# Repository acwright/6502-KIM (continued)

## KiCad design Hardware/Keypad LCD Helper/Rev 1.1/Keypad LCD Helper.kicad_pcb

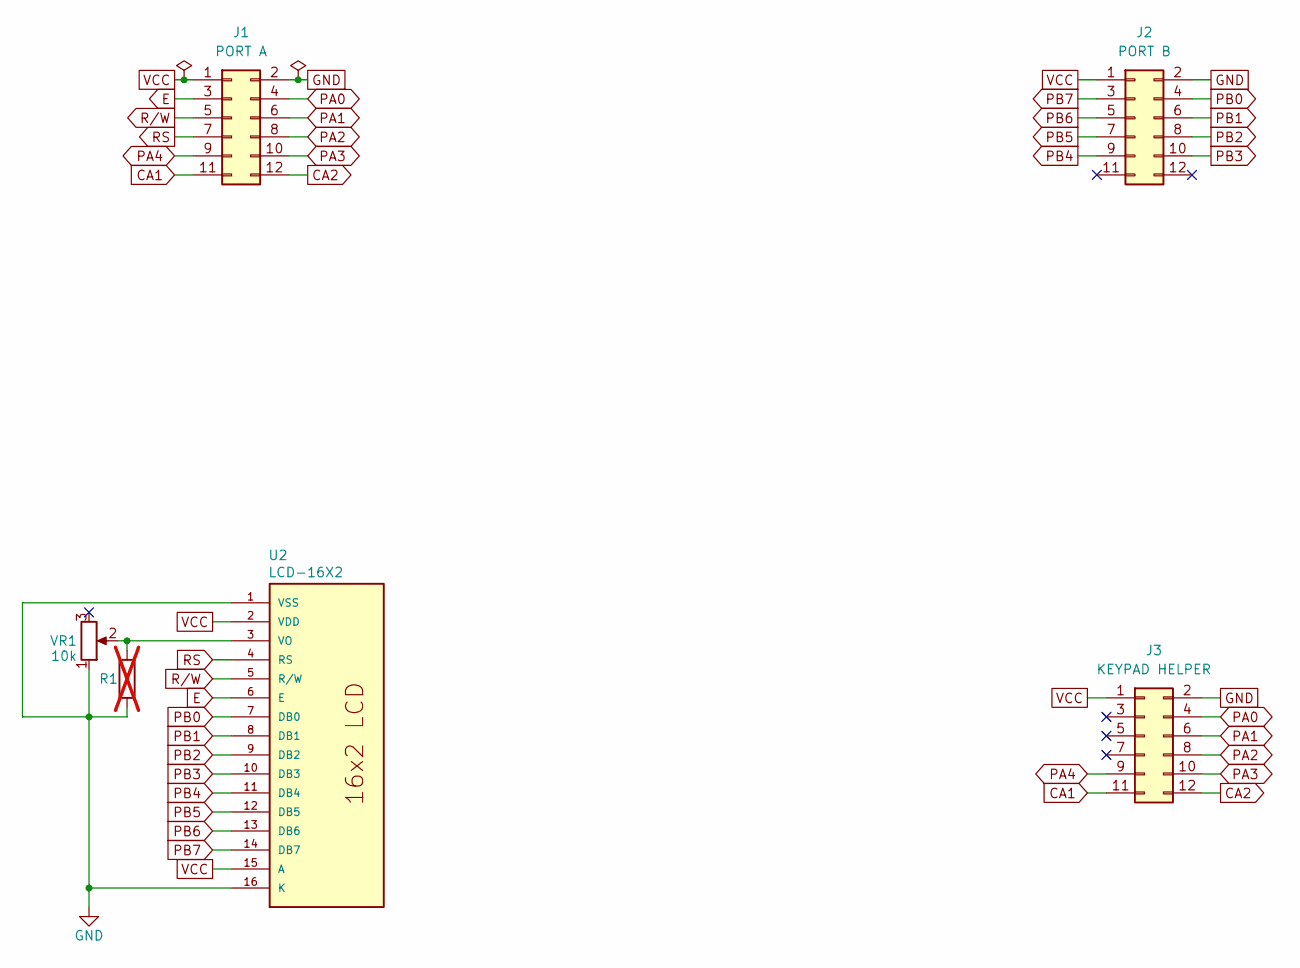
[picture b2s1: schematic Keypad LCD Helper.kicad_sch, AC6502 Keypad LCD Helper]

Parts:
J1: PORT A; 6502 GPIO Connector; Digikey 2057-BHR-12-VUA-ND
J2: PORT B; 6502 GPIO Connector; Digikey 2057-BHR-12-VUA-ND
J3: KEYPAD HELPER; 6502 GPIO Connector; Digikey 2057-BHR-12-VUA-ND
R1: DNP: parallel with VR1 to make ~10 k; R_Axial_DIN0204_L3.6mm_D1.6mm_P5.08mm_Horizontal; not fitted
U2: LCD-16X2
VR1: 10k; Trimmer 3386F; Digikey 3386F-103LF-ND

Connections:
CA1: J1.11, J3.11
CA2: J1.12, J3.12
E: J1.3, U2.6 (E)
GND: J1.2, J2.2, J3.2, R1.2, U2.1 (VSS), U2.16 (K), VR1.1
unnamed: R1.1, U2.3 (VO), VR1.2
PA0: J1.4, J3.4
PA1: J1.6, J3.6
PA2: J1.8, J3.8
PA3: J1.10, J3.10
PA4: J1.9, J3.9
PB0: J2.4, U2.7 (DB0)
PB1: J2.6, U2.8 (DB1)
PB2: J2.8, U2.9 (DB2)
PB3: J2.10, U2.10 (DB3)
PB4: J2.9, U2.11 (DB4)
PB5: J2.7, U2.12 (DB5)
PB6: J2.5, U2.13 (DB6)
PB7: J2.3, U2.14 (DB7)
RS: J1.7, U2.4 (RS)
R/W: J1.5, U2.5 (R/W)
VCC: J1.1, J2.1, J3.1, U2.2 (VDD), U2.15 (A)

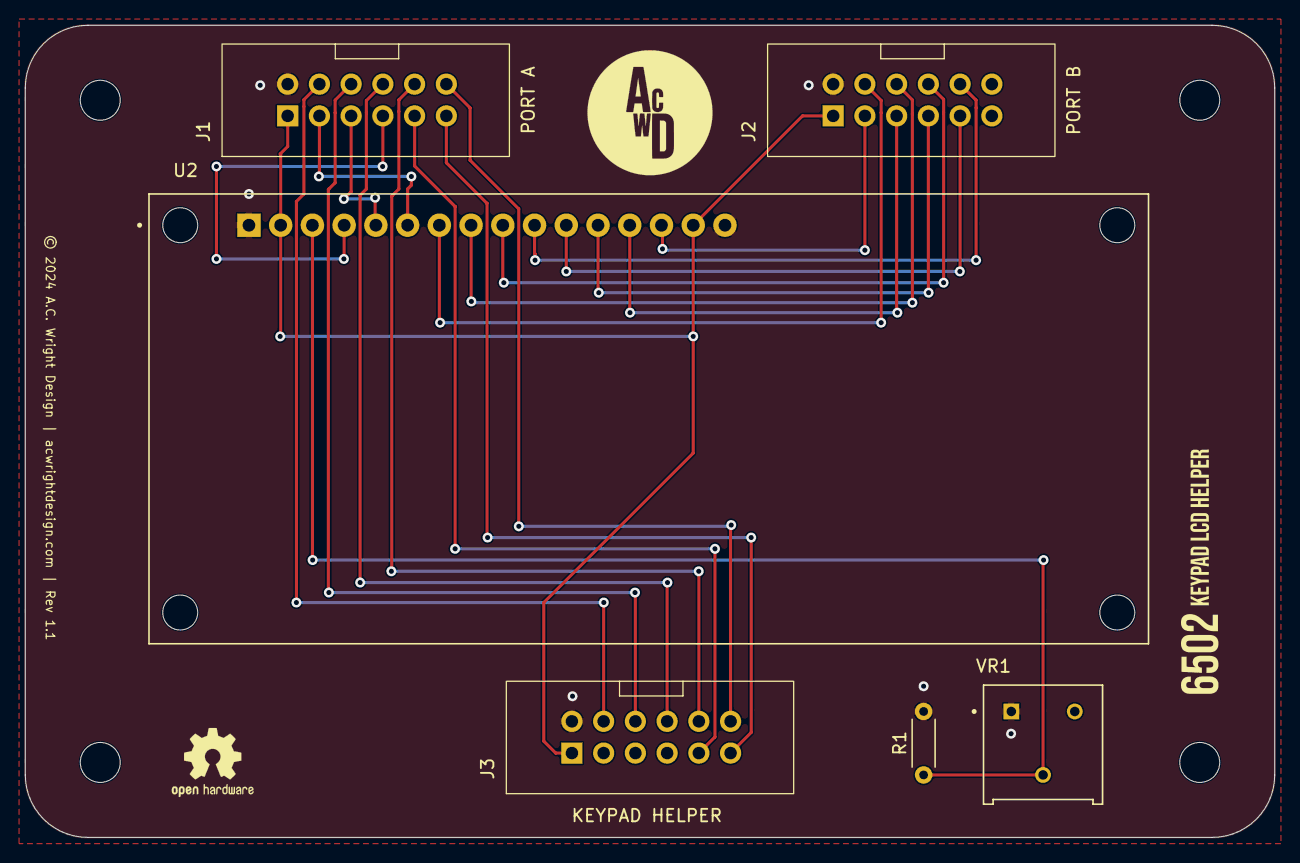
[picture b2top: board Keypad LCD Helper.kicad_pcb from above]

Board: 2 copper layers, 100.0 x 65.0 mm, 10 parts (0 on the bottom side), 21 nets.

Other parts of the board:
H1, H2, H3, H4: MountingHole; MountingHole_3.2mm_M3

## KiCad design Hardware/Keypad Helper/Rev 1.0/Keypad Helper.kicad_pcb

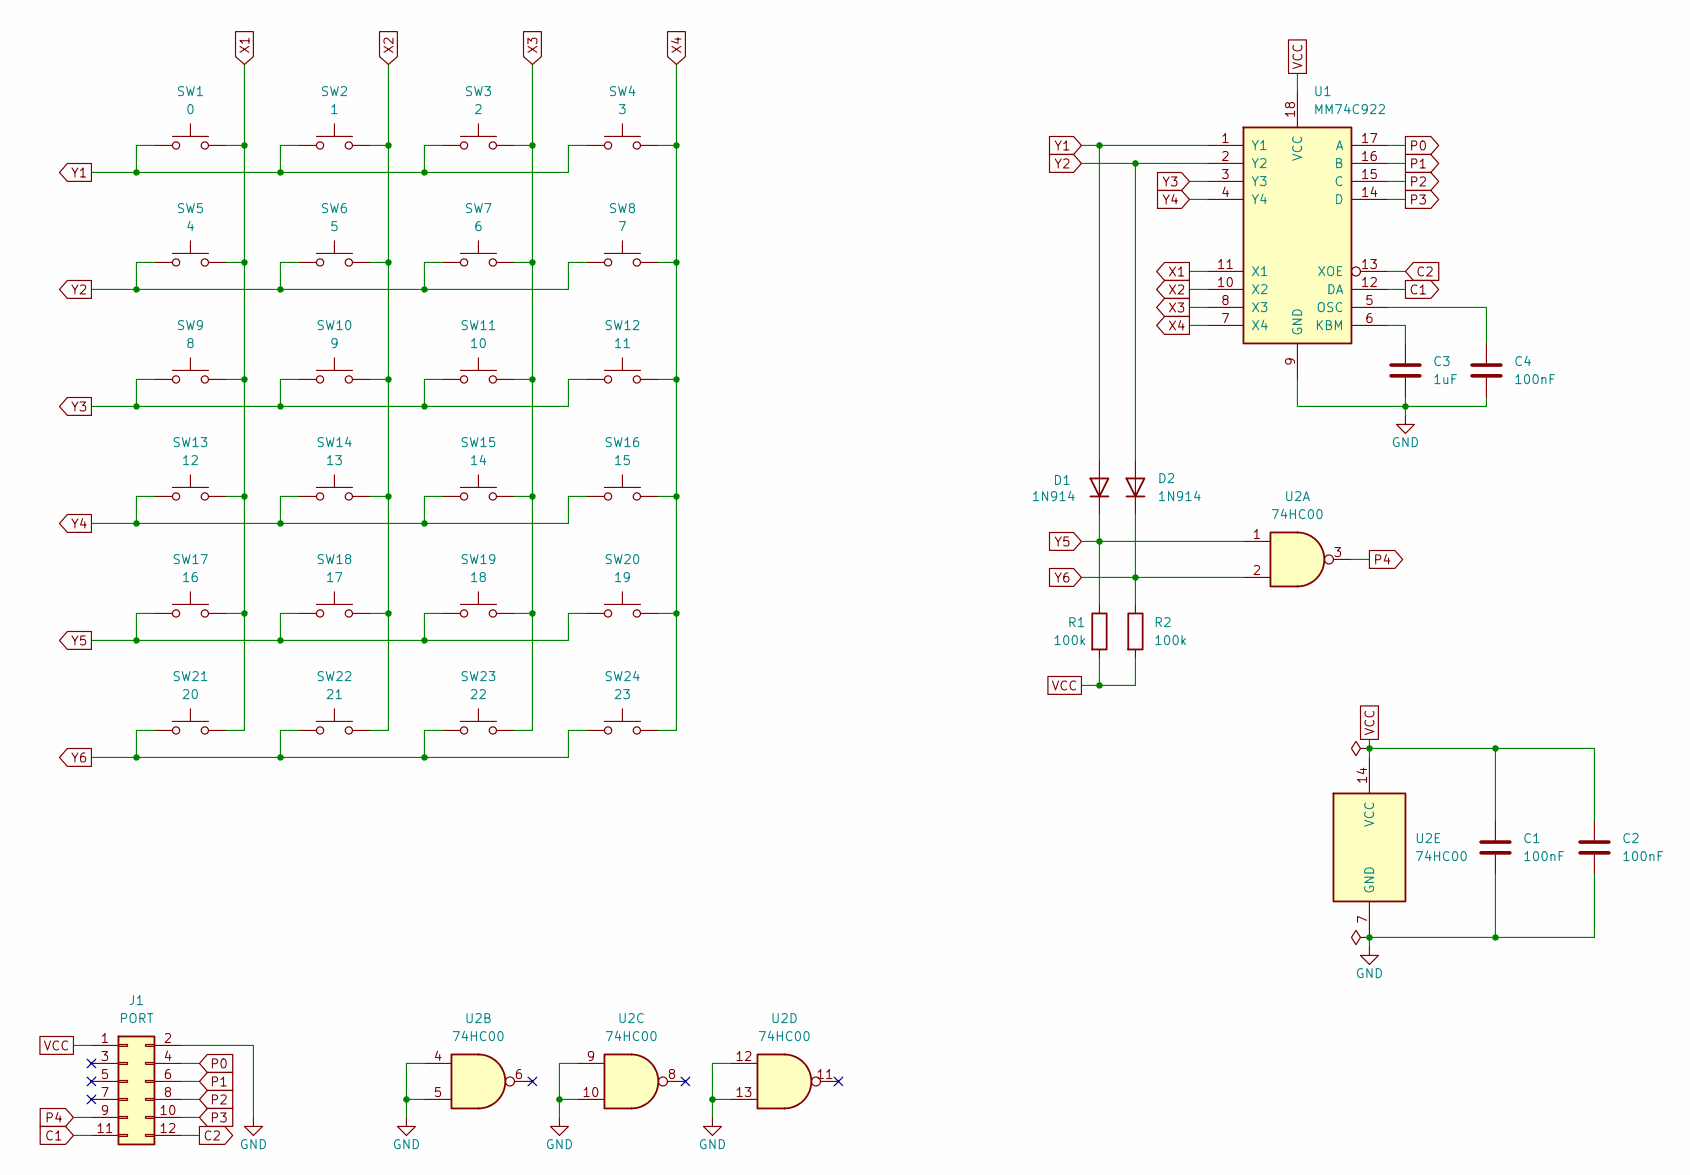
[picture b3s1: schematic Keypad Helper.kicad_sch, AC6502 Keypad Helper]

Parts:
C1, C2, C4: 100nF; C_Disc_D5.0mm_W2.5mm_P5.00mm; Digikey 478-3188-ND
C3: 1uF; C_Disc_D5.0mm_W2.5mm_P5.00mm; Digikey 478-SR215C105KAR-ND
D1, D2: 1N914; D_DO-35_SOD27_P7.62mm_Horizontal; Digikey 1N914FS-ND
J1: PORT; 6502 GPIO Connector; Digikey 2057-BHR-12-VUA-ND
R1, R2: 100k; R_Axial_DIN0204_L3.6mm_D1.6mm_P5.08mm_Horizontal; Digikey 13-MFR-12FTF52-100KCT-ND
SW1: 0; SW_Cherry_MX_1.00u_PCB; Digikey 1644-MX2A-E1NA-ND
SW2: 1; SW_Cherry_MX_1.00u_PCB; Digikey 1644-MX2A-E1NA-ND
SW3: 2; SW_Cherry_MX_1.00u_PCB; Digikey 1644-MX2A-E1NA-ND
SW4: 3; SW_Cherry_MX_1.00u_PCB; Digikey 1644-MX2A-E1NA-ND
SW5: 4; SW_Cherry_MX_1.00u_PCB; Digikey 1644-MX2A-E1NA-ND
SW6: 5; SW_Cherry_MX_1.00u_PCB; Digikey 1644-MX2A-E1NA-ND
SW7: 6; SW_Cherry_MX_1.00u_PCB; Digikey 1644-MX2A-E1NA-ND
SW8: 7; SW_Cherry_MX_1.00u_PCB; Digikey 1644-MX2A-E1NA-ND
SW9: 8; SW_Cherry_MX_1.00u_PCB; Digikey 1644-MX2A-E1NA-ND
SW10: 9; SW_Cherry_MX_1.00u_PCB; Digikey 1644-MX2A-E1NA-ND
SW11: 10; SW_Cherry_MX_1.00u_PCB; Digikey 1644-MX2A-E1NA-ND
SW12: 11; SW_Cherry_MX_1.00u_PCB; Digikey 1644-MX2A-E1NA-ND
SW13: 12; SW_Cherry_MX_1.00u_PCB; Digikey 1644-MX2A-E1NA-ND
SW14: 13; SW_Cherry_MX_1.00u_PCB; Digikey 1644-MX2A-E1NA-ND
SW15: 14; SW_Cherry_MX_1.00u_PCB; Digikey 1644-MX2A-E1NA-ND
SW16: 15; SW_Cherry_MX_1.00u_PCB; Digikey 1644-MX2A-E1NA-ND
SW17: 16; SW_Cherry_MX_1.00u_PCB; Digikey 1644-MX2A-E1NA-ND
SW18: 17; SW_Cherry_MX_1.00u_PCB; Digikey 1644-MX2A-E1NA-ND
SW19: 18; SW_Cherry_MX_1.00u_PCB; Digikey 1644-MX2A-E1NA-ND
SW20: 19; SW_Cherry_MX_1.00u_PCB; Digikey 1644-MX2A-E1NA-ND
SW21: 20; SW_Cherry_MX_1.00u_PCB; Digikey 1644-MX2A-E1NA-ND
SW22: 21; SW_Cherry_MX_1.00u_PCB; Digikey 1644-MX2A-E1NA-ND
SW23: 22; SW_Cherry_MX_1.00u_PCB; Digikey 1644-MX2A-E1NA-ND
SW24: 23; SW_Cherry_MX_1.00u_PCB; Digikey 1644-MX2A-E1NA-ND
U1: MM74C922; DIP-18_W7.62mm_LongPads
U2: 74HC00; DIP-14_W7.62mm_LongPads; Digikey 296-1563-5-ND

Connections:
C1: J1.11, U1.12 (DA)
C2: J1.12, U1.13 (XOE)
GND: C1.2, C2.2, C3.2, C4.2, J1.2, U1.9 (GND), U2.4, U2.5, U2.7 (GND), U2.9, U2.10, U2.12, U2.13
unnamed: C3.1, U1.6 (KBM)
unnamed: C4.1, U1.5 (OSC)
P0: J1.4, U1.17 (A)
P1: J1.6, U1.16 (B)
P2: J1.8, U1.15 (C)
P3: J1.10, U1.14 (D)
P4: J1.9, U2.3
VCC: C1.1, C2.1, J1.1, R1.2, R2.2, U1.18 (VCC), U2.14 (VCC)
X1: SW1.2, SW5.2, SW9.2, SW13.2, SW17.2, SW21.2, U1.11 (X1)
X2: SW2.2, SW6.2, SW10.2, SW14.2, SW18.2, SW22.2, U1.10 (X2)
X3: SW3.2, SW7.2, SW11.2, SW15.2, SW19.2, SW23.2, U1.8 (X3)
X4: SW4.2, SW8.2, SW12.2, SW16.2, SW20.2, SW24.2, U1.7 (X4)
Y1: D1.2 (A), SW1.1, SW2.1, SW3.1, SW4.1, U1.1 (Y1)
Y2: D2.2 (A), SW5.1, SW6.1, SW7.1, SW8.1, U1.2 (Y2)
Y3: SW9.1, SW10.1, SW11.1, SW12.1, U1.3 (Y3)
Y4: SW13.1, SW14.1, SW15.1, SW16.1, U1.4 (Y4)
Y5: D1.1 (K), R1.1, SW17.1, SW18.1, SW19.1, SW20.1, U2.1
Y6: D2.1 (K), R2.1, SW21.1, SW22.1, SW23.1, SW24.1, U2.2

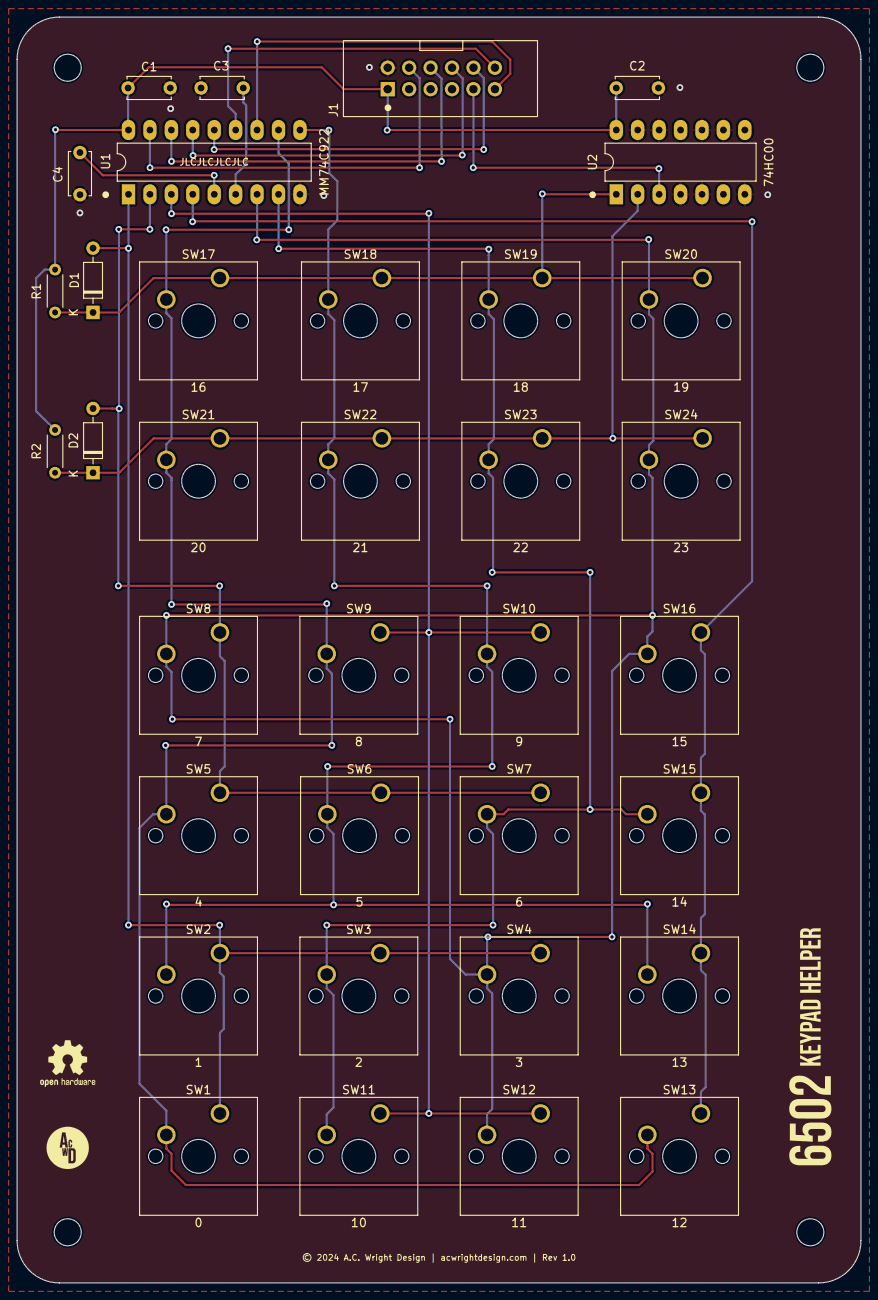
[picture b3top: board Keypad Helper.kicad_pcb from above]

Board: 2 copper layers, 100.0 x 150.0 mm, 39 parts (0 on the bottom side), 21 nets.

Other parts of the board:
H1, H2, H3, H4: MountingHole; MountingHole_3.2mm_M3

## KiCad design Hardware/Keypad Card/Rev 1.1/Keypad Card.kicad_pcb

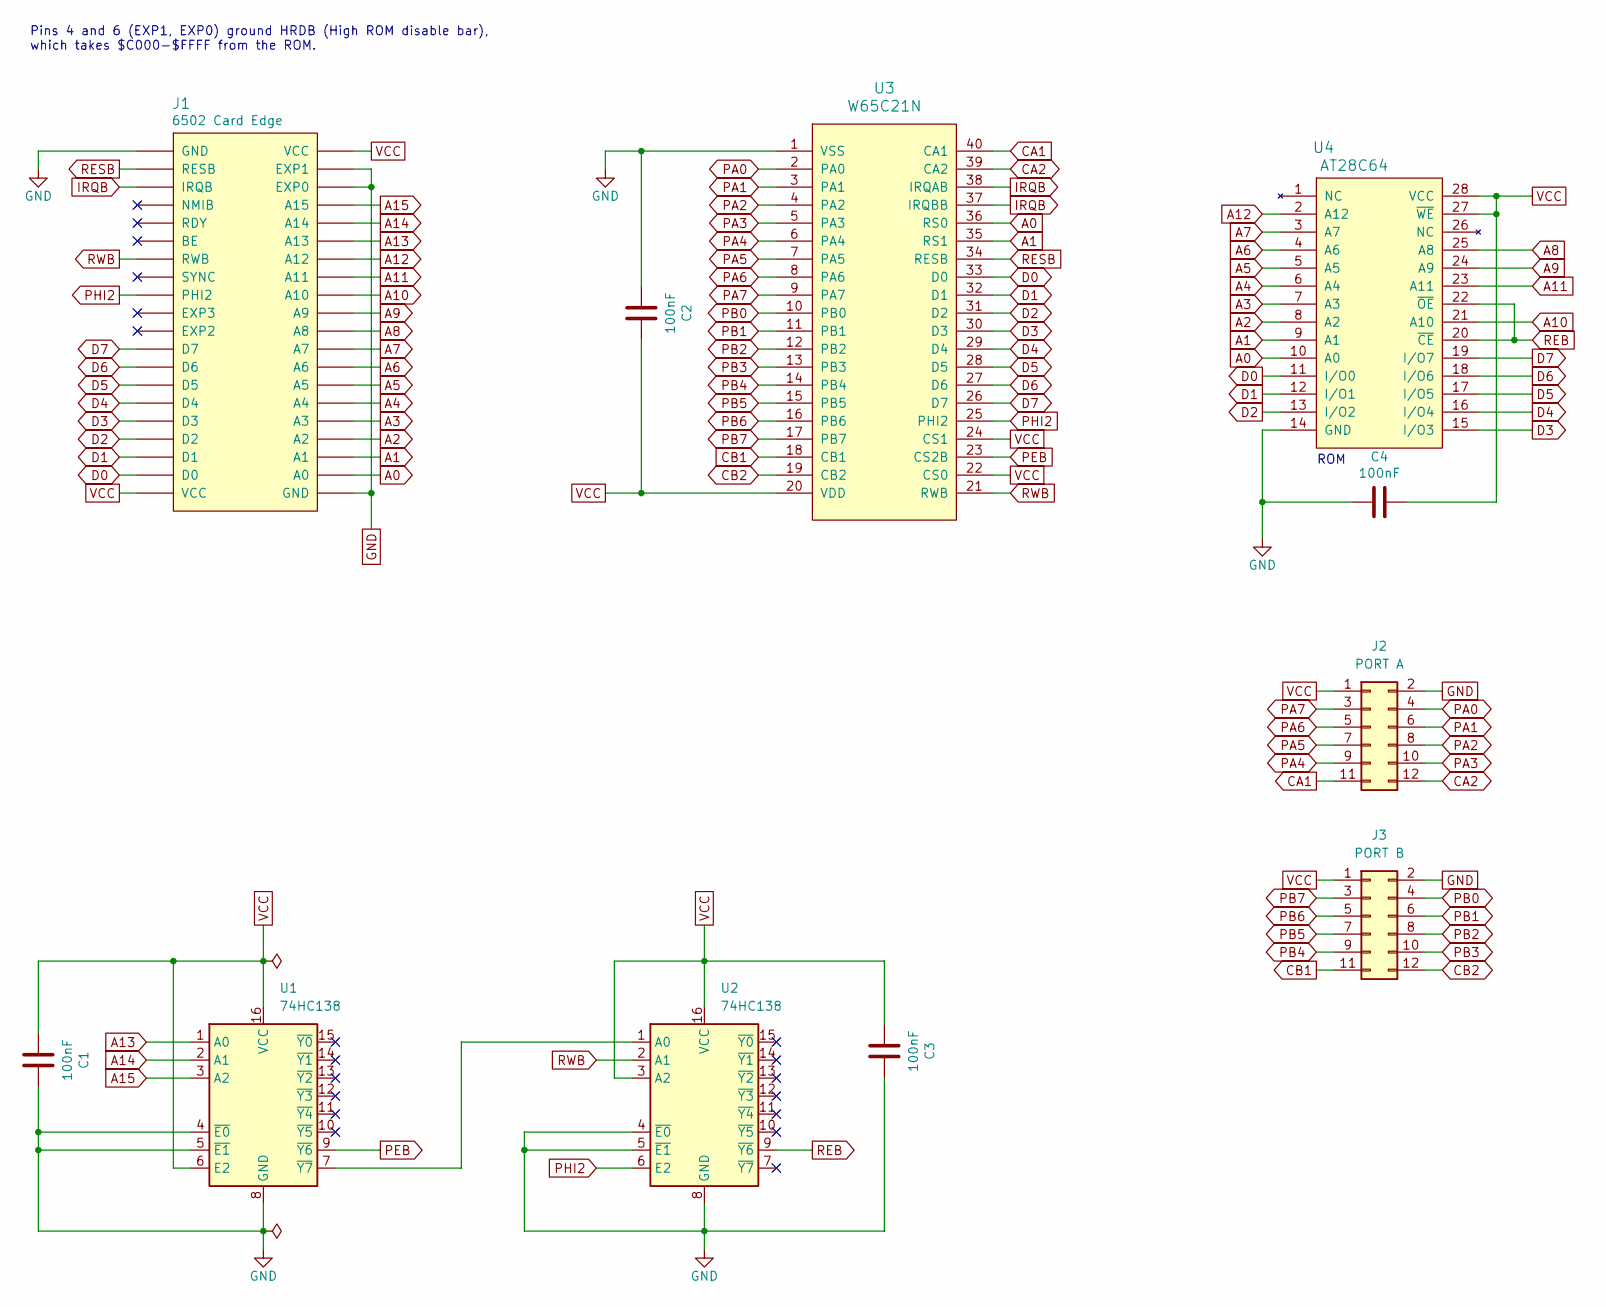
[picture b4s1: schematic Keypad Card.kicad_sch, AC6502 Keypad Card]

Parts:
C1, C2, C3, C4: 100nF; C_0805_2012Metric; LCSC C49678
J1: 6502 Card Edge
J2: PORT A; 6502 GPIO Connector; Digikey 2057-BHR-12-VUA-ND
J3: PORT B; 6502 GPIO Connector; Digikey 2057-BHR-12-VUA-ND
U1, U2: 74HC138; SOIC-16_3.9x9.9mm_P1.27mm; LCSC C5602
U3: W65C21N; DIP-40_W15.24mm_Socket_LongPads; Mouser 955-W65C21N6TPG-14
U4: AT28C64; DIP-28_W15.24mm_Socket_LongPads; Digikey AT28C64B-15PU-ND

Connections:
A0: J1.A0, U3.36 (RS0), U4.10 (A0)
A1: J1.A1, U3.35 (RS1), U4.9 (A1)
A2: J1.A2, U4.8 (A2)
A3: J1.A3, U4.7 (A3)
A4: J1.A4, U4.6 (A4)
A5: J1.A5, U4.5 (A5)
A6: J1.A6, U4.4 (A6)
A7: J1.A7, U4.3 (A7)
A8: J1.A8, U4.25 (A8)
A9: J1.A9, U4.24 (A9)
A10: J1.A10, U4.21 (A10)
A11: J1.A11, U4.23 (A11)
A12: J1.A12, U4.2 (A12)
A13: J1.A13, U1.1 (A0)
A14: J1.A14, U1.2 (A1)
A15: J1.A15, U1.3 (A2)
CA1: J2.11, U3.40 (CA1)
CA2: J2.12, U3.39 (CA2)
CB1: J3.11, U3.18 (CB1)
CB2: J3.12, U3.19 (CB2)
D0: J1.D0, U3.33 (D0), U4.11 (I/O0)
D1: J1.D1, U3.32 (D1), U4.12 (I/O1)
D2: J1.D2, U3.31 (D2), U4.13 (I/O2)
D3: J1.D3, U3.30 (D3), U4.15 (I/O3)
D4: J1.D4, U3.29 (D4), U4.16 (I/O4)
D5: J1.D5, U3.28 (D5), U4.17 (I/O5)
D6: J1.D6, U3.27 (D6), U4.18 (I/O6)
D7: J1.D7, U3.26 (D7), U4.19 (I/O7)
GND: C1.2, C2.1, C3.2, C4.2, J1.EXP0, J1.EXP1, J1.GND, J2.2, J3.2, U1.4 (~E0), U1.5 (~E1), U1.8 (GND), U2.4 (~E0), U2.5 (~E1), U2.8 (GND), U3.1 (VSS), U4.14 (GND)
IRQB: J1.IRQB, U3.37 (IRQBB), U3.38 (IRQAB)
unnamed: U1.7 (~Y7), U2.1 (A0)
PA0: J2.4, U3.2 (PA0)
PA1: J2.6, U3.3 (PA1)
PA2: J2.8, U3.4 (PA2)
PA3: J2.10, U3.5 (PA3)
PA4: J2.9, U3.6 (PA4)
PA5: J2.7, U3.7 (PA5)
PA6: J2.5, U3.8 (PA6)
PA7: J2.3, U3.9 (PA7)
PB0: J3.4, U3.10 (PB0)
PB1: J3.6, U3.11 (PB1)
PB2: J3.8, U3.12 (PB2)
PB3: J3.10, U3.13 (PB3)
PB4: J3.9, U3.14 (PB4)
PB5: J3.7, U3.15 (PB5)
PB6: J3.5, U3.16 (PB6)
PB7: J3.3, U3.17 (PB7)
PEB: U1.9 (~Y6), U3.23 (CS2B)
PHI2: J1.PHI2, U2.6 (E2), U3.25 (PHI2)
REB: U2.9 (~Y6), U4.20 (~CE), U4.22 (~OE)
RESB: J1.RESB, U3.34 (RESB)
RWB: J1.RWB, U2.2 (A1), U3.21 (RWB)
VCC: C1.1, C2.2, C3.1, C4.1, J1.VCC, J2.1, J3.1, U1.6 (E2), U1.16 (VCC), U2.3 (A2), U2.16 (VCC), U3.20 (VDD), U3.22 (CS0), U3.24 (CS1), U4.27 (~WE), U4.28 (VCC)

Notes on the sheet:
ROM
Pins 4 and 6 (EXP1, EXP0) ground HRDB (High ROM disable bar), which takes $C000-$FFFF from the ROM.

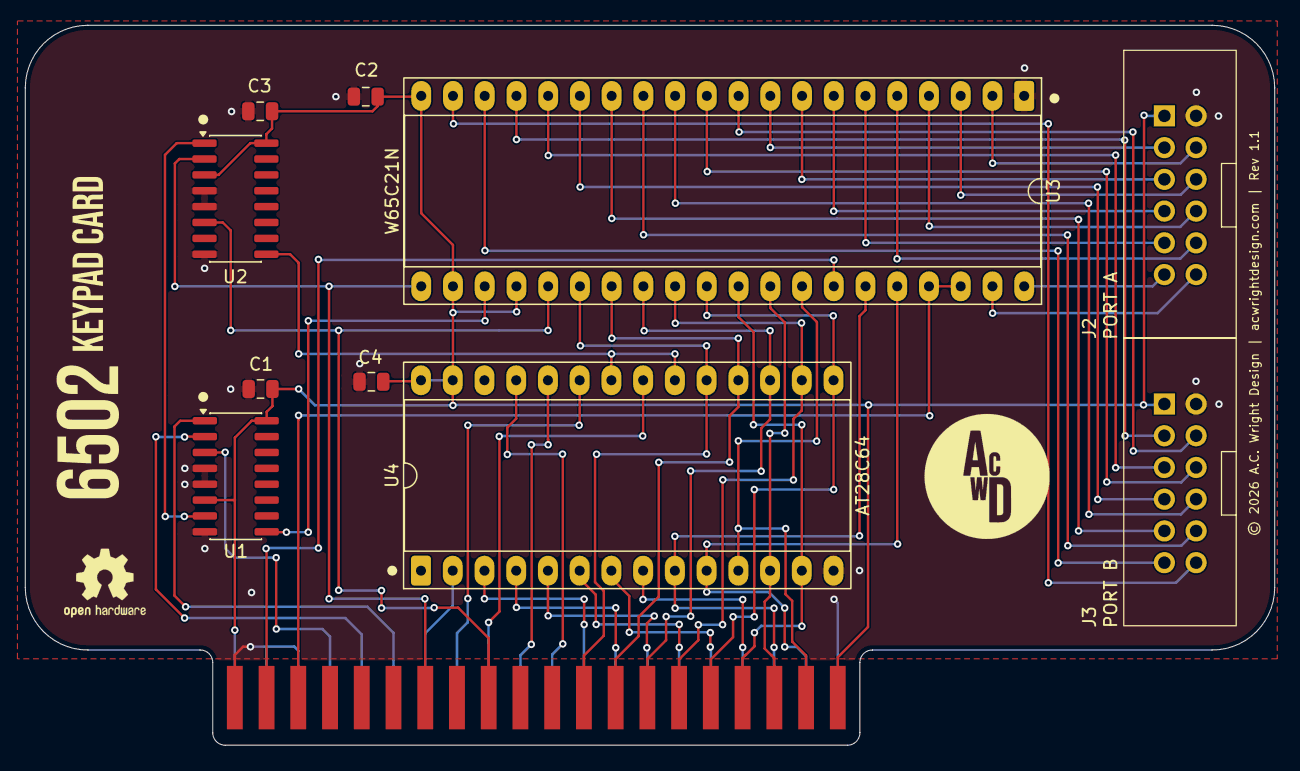
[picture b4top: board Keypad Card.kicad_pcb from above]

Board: 2 copper layers, 100.0 x 57.6 mm, 11 parts (0 on the bottom side), 53 nets.

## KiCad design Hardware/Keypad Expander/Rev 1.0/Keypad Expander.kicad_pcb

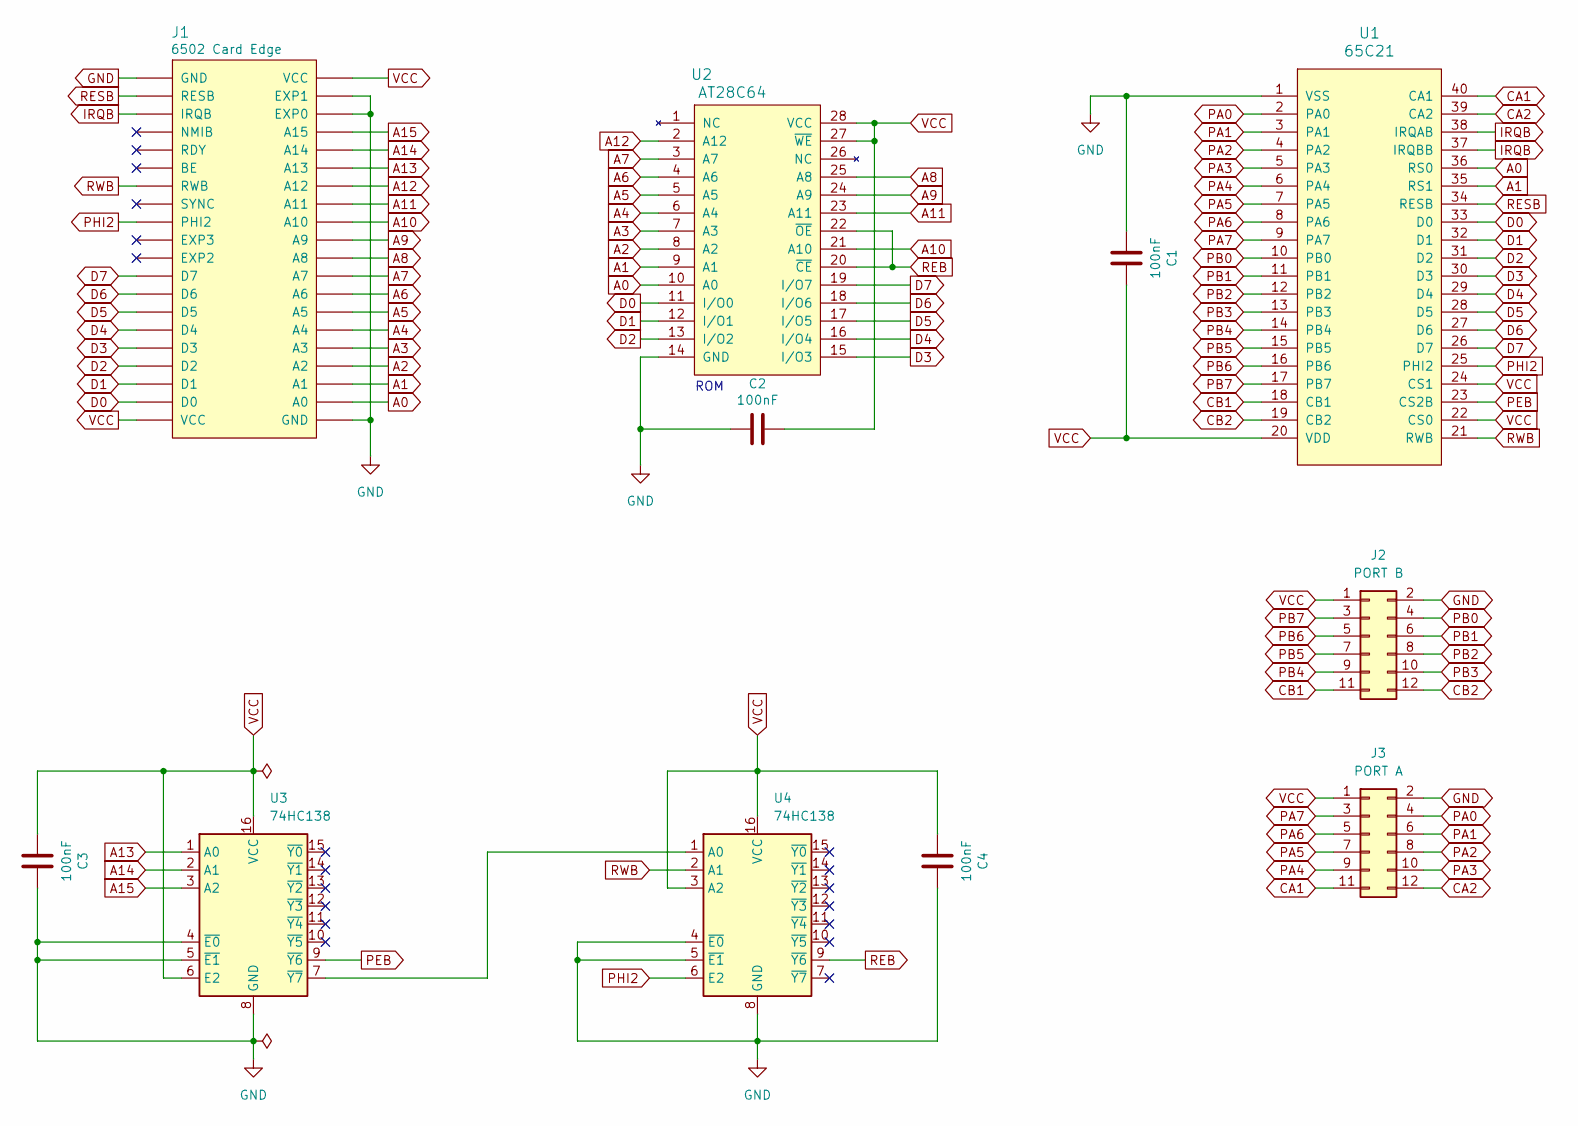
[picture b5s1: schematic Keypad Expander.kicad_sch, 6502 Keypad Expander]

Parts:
C1: 100nF; C_Disc_D5.0mm_W2.5mm_P5.00mm; LCSC C49678
C2, C3, C4: 100nF; C_Disc_D5.0mm_W2.5mm_P5.00mm
J1: 6502 Card Edge
J2: PORT B; 6502 GPIO Connector
J3: PORT A; 6502 GPIO Connector
U1: 65C21; DIP-40_W15.24mm_Socket_LongPads
U2: AT28C64; DIP-28_W15.24mm_Socket_LongPads
U3, U4: 74HC138; DIP-16_W7.62mm_Socket_LongPads

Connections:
A0: J1.A0, U1.36 (RS0), U2.10 (A0)
A1: J1.A1, U1.35 (RS1), U2.9 (A1)
A2: J1.A2, U2.8 (A2)
A3: J1.A3, U2.7 (A3)
A4: J1.A4, U2.6 (A4)
A5: J1.A5, U2.5 (A5)
A6: J1.A6, U2.4 (A6)
A7: J1.A7, U2.3 (A7)
A8: J1.A8, U2.25 (A8)
A9: J1.A9, U2.24 (A9)
A10: J1.A10, U2.21 (A10)
A11: J1.A11, U2.23 (A11)
A12: J1.A12, U2.2 (A12)
A13: J1.A13, U3.1 (A0)
A14: J1.A14, U3.2 (A1)
A15: J1.A15, U3.3 (A2)
CA1: J3.11, U1.40 (CA1)
CA2: J3.12, U1.39 (CA2)
CB1: J2.11, U1.18 (CB1)
CB2: J2.12, U1.19 (CB2)
D0: J1.D0, U1.33 (D0), U2.11 (I/O0)
D1: J1.D1, U1.32 (D1), U2.12 (I/O1)
D2: J1.D2, U1.31 (D2), U2.13 (I/O2)
D3: J1.D3, U1.30 (D3), U2.15 (I/O3)
D4: J1.D4, U1.29 (D4), U2.16 (I/O4)
D5: J1.D5, U1.28 (D5), U2.17 (I/O5)
D6: J1.D6, U1.27 (D6), U2.18 (I/O6)
D7: J1.D7, U1.26 (D7), U2.19 (I/O7)
GND: C1.1, C2.2, C3.2, C4.2, J1.EXP0, J1.EXP1, J1.GND, J2.2, J3.2, U1.1 (VSS), U2.14 (GND), U3.4 (~E0), U3.5 (~E1), U3.8 (GND), U4.4 (~E0), U4.5 (~E1), U4.8 (GND)
IRQB: J1.IRQB, U1.37 (IRQBB), U1.38 (IRQAB)
unnamed: U3.7 (~Y7), U4.1 (A0)
PA0: J3.4, U1.2 (PA0)
PA1: J3.6, U1.3 (PA1)
PA2: J3.8, U1.4 (PA2)
PA3: J3.10, U1.5 (PA3)
PA4: J3.9, U1.6 (PA4)
PA5: J3.7, U1.7 (PA5)
PA6: J3.5, U1.8 (PA6)
PA7: J3.3, U1.9 (PA7)
PB0: J2.4, U1.10 (PB0)
PB1: J2.6, U1.11 (PB1)
PB2: J2.8, U1.12 (PB2)
PB3: J2.10, U1.13 (PB3)
PB4: J2.9, U1.14 (PB4)
PB5: J2.7, U1.15 (PB5)
PB6: J2.5, U1.16 (PB6)
PB7: J2.3, U1.17 (PB7)
PEB: U1.23 (CS2B), U3.9 (~Y6)
PHI2: J1.PHI2, U1.25 (PHI2), U4.6 (E2)
REB: U2.20 (~CE), U2.22 (~OE), U4.9 (~Y6)
RESB: J1.RESB, U1.34 (RESB)
RWB: J1.RWB, U1.21 (RWB), U4.2 (A1)
VCC: C1.2, C2.1, C3.1, C4.1, J1.VCC, J2.1, J3.1, U1.20 (VDD), U1.22 (CS0), U1.24 (CS1), U2.27 (~WE), U2.28 (VCC), U3.6 (E2), U3.16 (VCC), U4.3 (A2), U4.16 (VCC)

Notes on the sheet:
ROM

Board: 2 copper layers, 17 parts (0 on the bottom side), 53 nets, no tracks yet.

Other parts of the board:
H1, H1#2, H2, H2#2: MountingHole; MountingHole_3.2mm_M3
H3, H4: MountingHole; MountingHole_2.2mm_M2

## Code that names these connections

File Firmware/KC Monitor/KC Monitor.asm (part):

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;   LCD DRIVER
; =============================================================================
;   HD44780-compatible 16x2 display in 8-bit mode.  Port B carries the data
;   bus; Port A carries RS/R-W/E on PA5/PA6/PA7.  Command/data writes use
;   timed software delays instead of busy-flag polling (the R/W read-back
;   path is not relied upon).
; =============================================================================
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;   LcdDelay — short software busy delay (~640 us @ 1 MHz)
; -----------------------------------------------------------------------------
;   Used in place of busy-flag polling so the driver does not depend on the
;   LCD R/W read-back path (PA6) working.  An HD44780 finishes a normal
;   command/data write in ~37 us, so this single ~640 us loop carries a wide
;   margin while staying short enough that a full RefreshDisplay (~34 writes)
;   completes in ~22 ms — fast enough to keep the keypad responsive.  Callers
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;   Modifies: A, X, Y
; -----------------------------------------------------------------------------
LcdInit:
  ; Port A: PA5-7 outputs (LCD control), PA0-4 inputs (keypad code)
  lda #CR_DDR
  sta CRA
  lda #LCD_DDRA
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; =============================================================================
;   KEYPAD DRIVER
; =============================================================================
;   The 74C922 keypad encoder drives PA0-PA4 with a 5-bit keycode and pulses
;   CA1 (positive edge) when a key becomes available.  CA2 is held low to
;   enable the encoder's active-low output enable.  Key entry is interrupt
;   driven: the CA1 edge fires KeyIrq, which latches the keycode into a small
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; -----------------------------------------------------------------------------
;   PiaInit — configure the PIA for keypad input (and Port B for LCD data)
; -----------------------------------------------------------------------------
;   Sets DDRA so PA5-7 are outputs (LCD control) and PA0-4 inputs (keycode),
;   DDRB all outputs (LCD data bus), then writes the keypad CRA value which
;   enables the 74C922 (CA2 low) and arms CA1 on the positive edge with its
;   interrupt ENABLED.  The CPU IRQ must stay masked until the caller is
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;   Modifies: A
; -----------------------------------------------------------------------------
PiaInit:
  ; Port A direction: PA5-7 outputs, PA0-4 inputs
  lda #CR_DDR
  sta CRA
  lda #LCD_DDRA                 ; $E0
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  and #PIA_CA1_FLAG             ; keypad data-available?
  beq @Serial                   ; no keypad edge — go drain the serial card
  lda PORTA                     ; latch keycode (also clears the CA1 flag)
  and #KEY_MASK                 ; keep PA0-4 (0-31)
  cmp #KEY_ESC                  ; ESC is a break-to-monitor abort
  beq @Esc                      ; -> WarmStart, never reaches the mailbox
  cmp #KEY_COUNT
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  ldx #SC_CMD_RTS_LOW
  cmp #SC_RTS_LOW_WATER
  bcc ScRtsWrite                ; drained — let it talk again
  rts                           ; between the marks — leave the pin as it is

; -----------------------------------------------------------------------------
;   ScRtsLow — lower RTS, which is also what turns the transmitter back on
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
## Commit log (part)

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2026-05-05 Cleanup project
2026-05-09 Finish Keypad Expander layout
2026-05-10 Working on KIM Board
2026-05-10 Remove KIM Board
2026-05-10 Add Keypad Card
2026-05-11 Finish Keypad Card
2026-05-11 Production fix
2026-05-16 Add BOMs
2026-05-19 Finish BOM and add BOM to README
2026-05-19 Restore exclude from BOM
2026-05-19 Update BOM
2026-05-30 Finish initial KC Monitor ROM
2026-06-05 Add keycaps document
2026-06-11 Fix keypress timing
2026-06-11 README fix
2026-06-16 Remove BOM CSV's
2026-06-21 Silkscreen fix

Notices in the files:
Hardware/Keypad Card/Rev 1.1/Keypad Card.kicad_pcb:
© 2026 A.C. Wright Design | acwrightdesign.com | Rev 1.1
Hardware/Keypad Expander/Rev 1.0/Keypad Expander.kicad_pcb:
© 2026 A.C. Wright Design | acwrightdesign.com | Rev 0
Hardware/Keypad Helper/Rev 1.0/Keypad Helper.kicad_pcb:
© 2024 A.C. Wright Design | acwrightdesign.com | Rev 1.0
Hardware/Keypad LCD Helper/Rev 1.1/Keypad LCD Helper.kicad_pcb:
© 2024 A.C. Wright Design | acwrightdesign.com | Rev 1.1
